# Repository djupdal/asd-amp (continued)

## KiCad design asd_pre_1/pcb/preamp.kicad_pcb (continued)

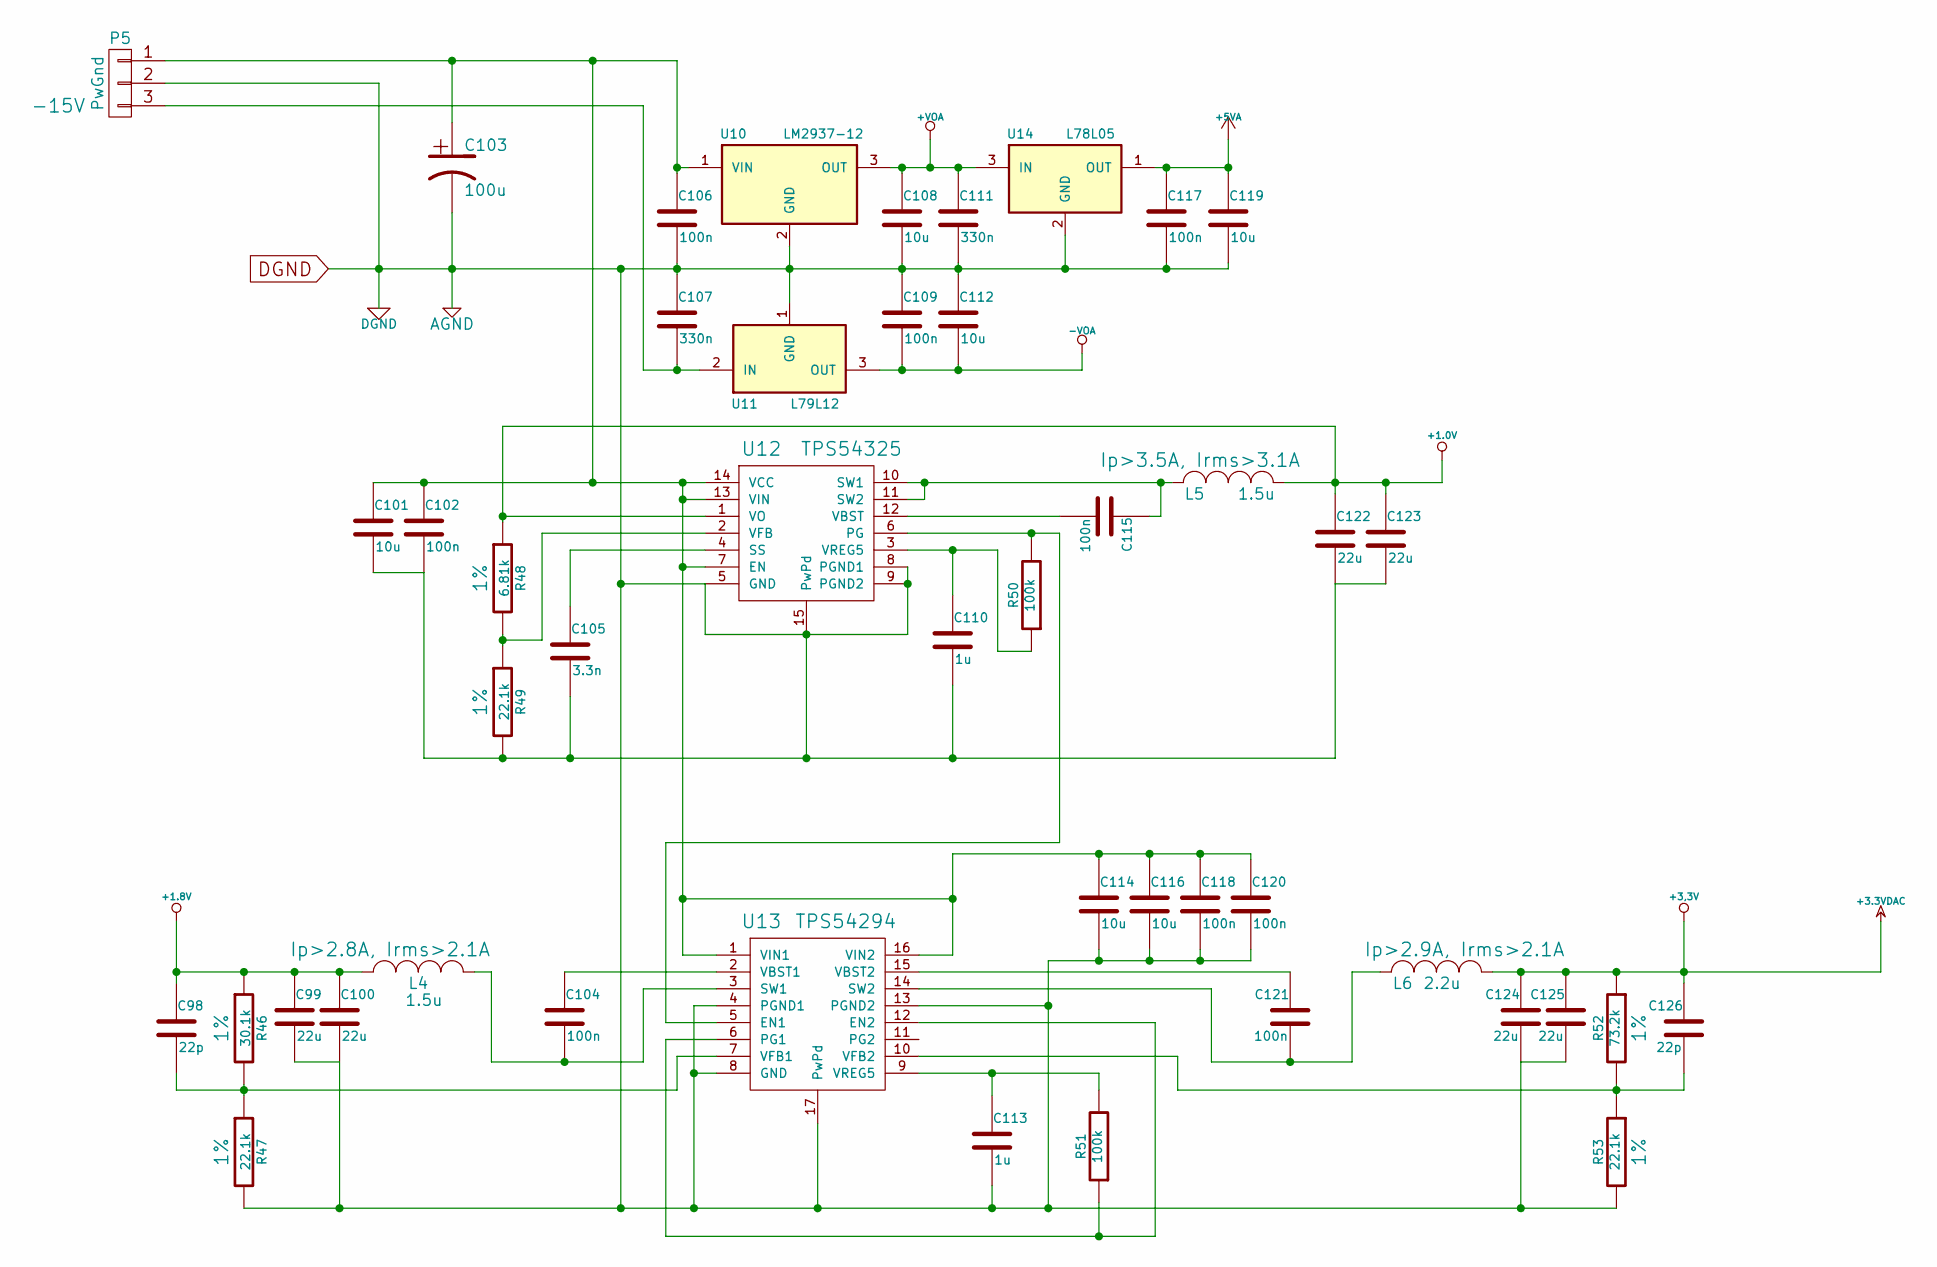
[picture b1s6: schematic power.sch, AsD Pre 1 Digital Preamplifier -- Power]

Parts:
C98, C126: 22p; C_0603_HandSoldering
C99, C100, C122, C123, C124, C125: 22u; C_0805_HandSoldering
C101, C108, C112, C114, C116, C119: 10u; C_0805_HandSoldering
C102, C104, C106, C109, C115, C117, C118, C120, C121: 100n; C_0603_HandSoldering
C103: 100u; TantalC_SizeB_EIA-3528_HandSoldering
C105: 3.3n; C_0603_HandSoldering
C107, C111: 330n; C_0603_HandSoldering
C110, C113: 1u; C_0805_HandSoldering
L4, L5: 1.5u; SPM3015
L6: 2.2u; SPM3015
P5: PwGnd; Terminal_Block_3_5mm
R46: 30.1k; R_0805_HandSoldering
R47, R49, R53: 22.1k; R_0805_HandSoldering
R48: 6.81k; R_0805_HandSoldering
R50, R51: 100k; R_0805_HandSoldering
R52: 73.2k; R_0805_HandSoldering
U10: LM2937-12; SOT-223
U11: L79L12; SOT89-3_Housing_Handsoldering
U12: TPS54325; TSSOP-14_4.4x5mm_Pitch0.65mm_exposed_pad
U13: TPS54294; TSSOP-16-1EP_4.4x5mm_Pitch0.65mm
U14: L78L05; SOT89-3_Housing_Handsoldering

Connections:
+1.0V: C122.1, C123.1, L5.2, R48.1, U12.1 (VO); also elsewhere on the board
+1.8V: C98.1, C99.1, C100.1, L4.1, R46.1; also elsewhere on the board
+3.3V: C124.1, C125.1, C126.1, L6.1, R52.1; also elsewhere on the board
+5VA: C117.1, C119.1, U14.1 (OUT); also elsewhere on the board
+VOA: C108.1, C111.1, U10.3 (OUT), U14.3 (IN); also elsewhere on the board
-VOA: C109.2, C112.2, U11.3 (OUT); also elsewhere on the board
DGND: C99.2, C100.2, C101.2, C102.2, C103.2, C105.2, C106.2, C107.1, C108.2, C109.1, C110.2, C111.2, C112.1, C113.2, C114.2, C116.2, C117.2, C118.2, C119.2, C120.2, C122.2, C123.2, C124.2, C125.2, P5.2, R47.2, R49.2, R53.2, U10.2 (GND), U11.1 (GND), U12.5 (GND), U12.8 (PGND1), U12.9 (PGND2), U12.15 (PwPd), U13.4 (PGND1), U13.8 (GND), U13.13 (PGND2), U13.17 (PwPd), U14.2 (GND); also elsewhere on the board
unnamed: C98.2, R46.2, R47.1, U13.7 (VFB1)
unnamed: C101.1, C102.1, C103.1, C106.1, C114.1, C116.1, C118.1, C120.1, P5.1, U10.1 (VIN), U12.7 (EN), U12.13 (VIN), U12.14 (VCC), U13.1 (VIN1), U13.16 (VIN2)
unnamed: C104.1, U13.2 (VBST1)
unnamed: C104.2, L4.2, U13.3 (SW1)
unnamed: C105.1, U12.4 (SS)
unnamed: C107.2, P5.3, U11.2 (IN)
unnamed: C110.1, R50.1, U12.3 (VREG5)
unnamed: C113.1, R51.2, U13.9 (VREG5)
unnamed: C115.1, L5.1, U12.10 (SW1), U12.11 (SW2)
unnamed: C115.2, U12.12 (VBST)
unnamed: C121.1, U13.15 (VBST2)
unnamed: C121.2, L6.2, U13.14 (SW2)
unnamed: C126.2, R52.2, R53.1, U13.10 (VFB2)
unnamed: R48.2, R49.1, U12.2 (VFB)
unnamed: R50.2, U12.6 (PG), U13.5 (EN1)
unnamed: R51.1, U13.6 (PG1), U13.12 (EN2)

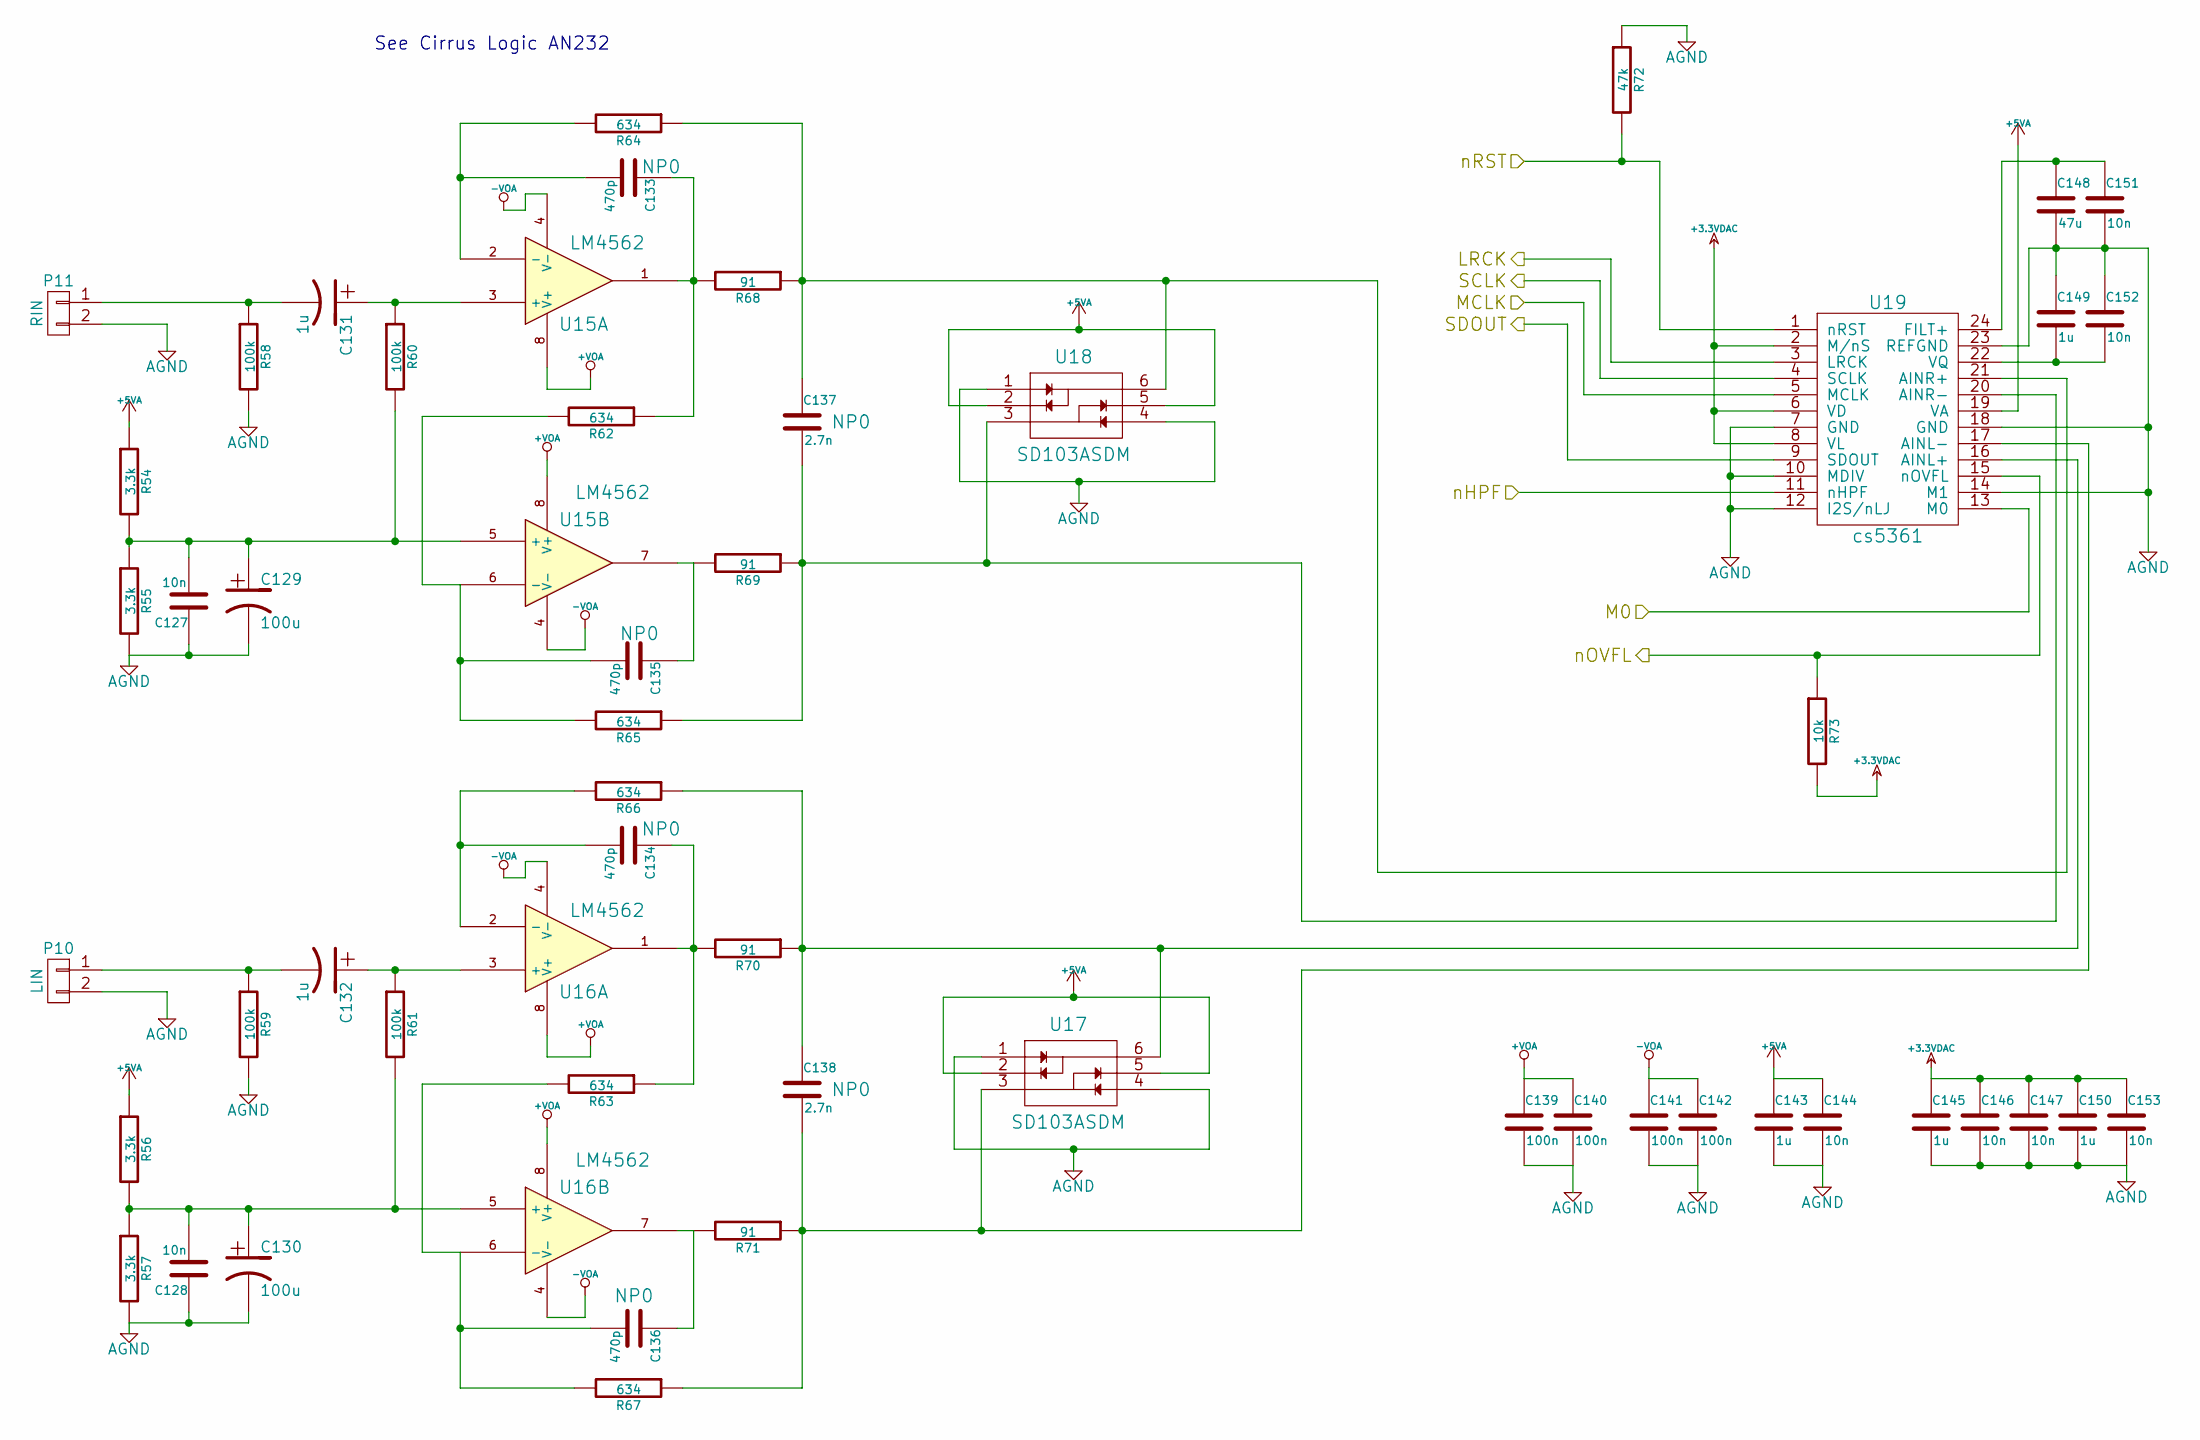
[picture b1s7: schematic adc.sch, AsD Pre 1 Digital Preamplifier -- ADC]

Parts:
C127, C128, C144, C146, C147, C151, C152, C153: 10n; C_0603_HandSoldering
C129, C130: 100u; TantalC_SizeB_EIA-3528_HandSoldering
C131, C132, C143, C145, C149, C150: 1u; C_0805_HandSoldering
C133, C134, C135, C136: 470p; C_0603_HandSoldering
C137, C138: 2.7n; C_0603_HandSoldering
C139, C140, C141, C142: 100n; C_0603_HandSoldering
C148: 47u; C_1210_HandSoldering
P10: LIN; Terminal_Block_2_2.5mm
P11: RIN; Terminal_Block_2_2.5mm
R54, R55, R56, R57: 3.3k; R_0805_HandSoldering
R58, R59, R60, R61: 100k; R_0805_HandSoldering
R62, R63, R64, R65, R66, R67: 634; R_0805_HandSoldering
R68, R69, R70, R71: 91; R_0805_HandSoldering
R72: 47k; R_0805_HandSoldering
R73: 10k; R_0805_HandSoldering
U15, U16: LM4562; SOIC-8-W
U17, U18: SD103ASDM; SOT-26-6
U19: cs5361; TSSOP-24_4.4x7.8mm_Pitch0.65mm

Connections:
+3.3V: C145.1, C146.1, C147.1, C150.1, C153.1, R73.2, U19.2 (M/nS), U19.6 (VD), U19.8 (VL); also elsewhere on the board
+5VA: C143.1, C144.1, R54.1, R56.1, U17.2, U17.5, U18.2, U18.5, U19.19 (VA); also elsewhere on the board
+VOA: C139.1, C140.1, U15.8 (V+), U16.8 (V+); also elsewhere on the board
-VOA: C141.1, C142.1, U15.4 (V-), U16.4 (V-); also elsewhere on the board
/ADC/LRCK: U19.3 (LRCK); also elsewhere on the board
/ADC/M0: U19.13 (M0); also elsewhere on the board
/ADC/MCLK: U19.5 (MCLK); also elsewhere on the board
/ADC/nHPF: U19.11 (nHPF); also elsewhere on the board
/ADC/nOVFL: R73.1, U19.15 (nOVFL); also elsewhere on the board
/ADC/nRST: R72.2, U19.1 (nRST); also elsewhere on the board
/FPGA/BCKI2: U19.4 (SCLK); also elsewhere on the board
/FPGA/DIN2: U19.9 (SDOUT); also elsewhere on the board
DGND: C127.1, C128.1, C129.2, C130.2, C139.2, C140.2, C141.2, C142.2, C143.2, C144.2, C145.2, C146.2, C147.2, C148.2, C149.1, C150.2, C151.2, C152.1, C153.2, P10.2, P11.2, R55.2, R57.2, R58.2, R59.2, R72.1, U17.1, U17.4, U18.1, U18.4, U19.7 (GND), U19.10 (MDIV), U19.12 (I2S/nLJ), U19.14 (M1), U19.18 (GND), U19.23 (REFGND); also elsewhere on the board
unnamed: C127.2, C129.1, R54.2, R55.1, R60.2, U15.5 (+)
unnamed: C128.2, C130.1, R56.2, R57.1, R61.2, U16.5 (+)
unnamed: C131.1, R60.1, U15.3 (+)
unnamed: C131.2, P11.1, R58.1
unnamed: C132.1, R61.1, U16.3 (+)
unnamed: C132.2, P10.1, R59.1
unnamed: C133.1, R62.1, R68.2, U15.1
unnamed: C133.2, R64.2, U15.2 (-)
unnamed: C134.1, R63.1, R70.2, U16.1
unnamed: C134.2, R66.2, U16.2 (-)
unnamed: C135.1, R69.2, U15.7
unnamed: C135.2, R62.2, R65.2, U15.6 (-)
unnamed: C136.1, R71.2, U16.7
unnamed: C136.2, R63.2, R67.2, U16.6 (-)
unnamed: C137.1, R64.1, R68.1, U18.6, U19.21 (AINR+)
unnamed: C137.2, R65.1, R69.1, U18.3, U19.20 (AINR-)
unnamed: C138.1, R66.1, R70.1, U17.6, U19.16 (AINL+)
unnamed: C138.2, R67.1, R71.1, U17.3, U19.17 (AINL-)
unnamed: C148.1, C151.1, U19.24 (FILT+)
unnamed: C149.2, C152.2, U19.22 (VQ)

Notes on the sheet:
See Cirrus Logic AN232

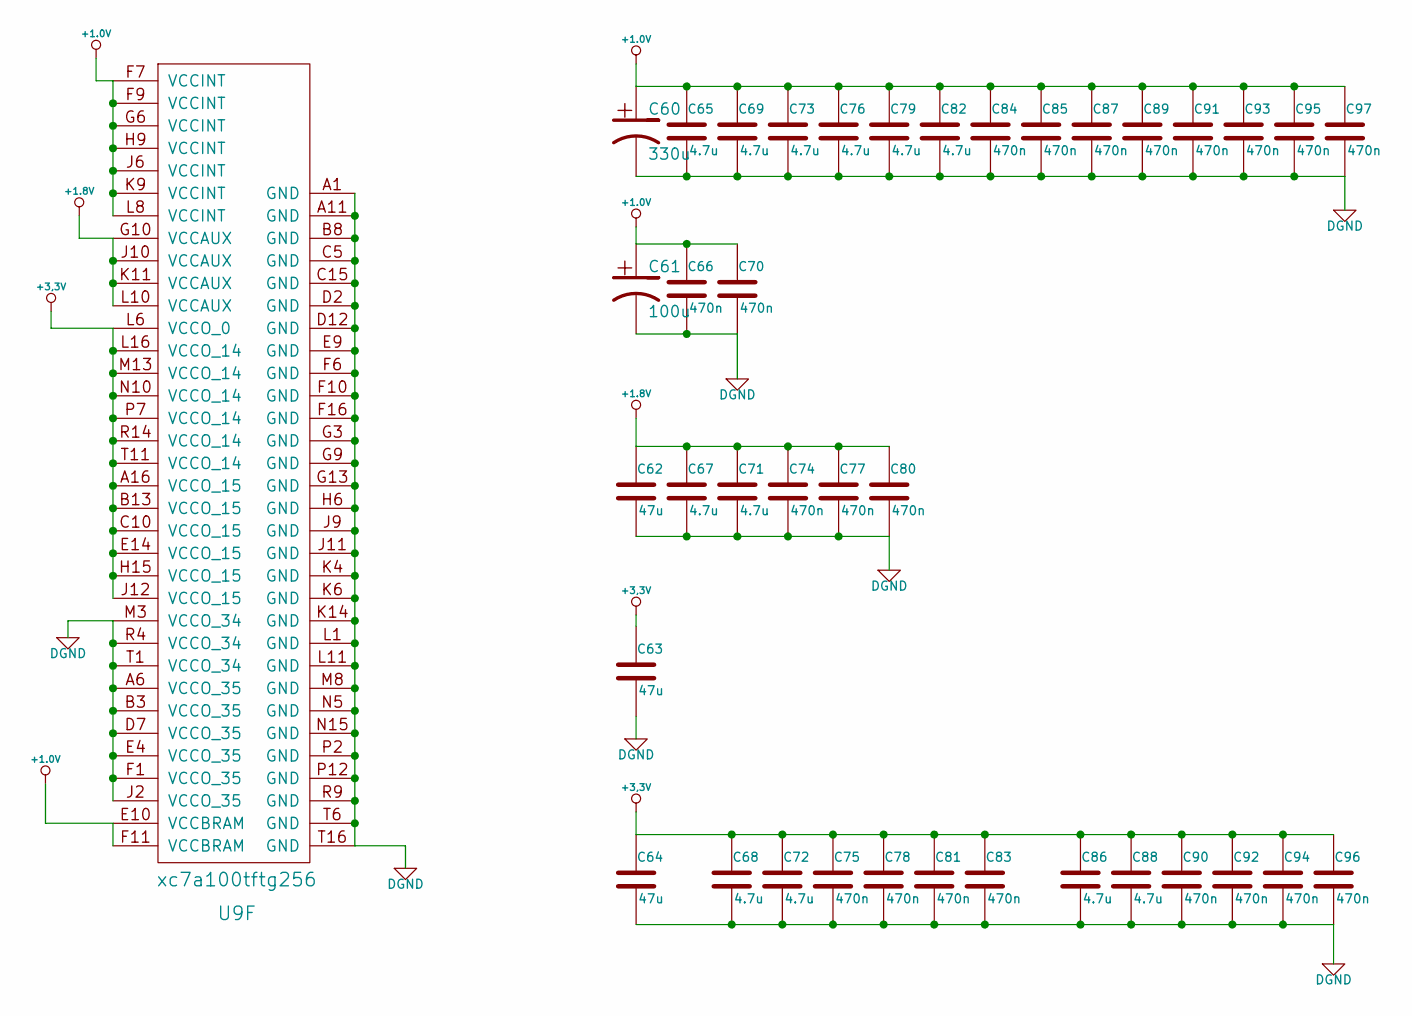
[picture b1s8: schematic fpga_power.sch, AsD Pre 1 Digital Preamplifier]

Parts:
C60: 330u; TantalC_SizeD_EIA-7343_HandSoldering
C61: 100u; TantalC_SizeB_EIA-3528_HandSoldering
C62, C63, C64: 47u; C_1210_HandSoldering
C65, C67, C68, C69, C71, C72, C73, C76, C79, C82, C86, C88: 4.7u; C_0805_HandSoldering
C66, C70, C74, C75, C77, C78, C80, C81, C83, C84, C85, C87, C89, C90, C91, C92, C93, C94, C95, C96, C97: 470n; C_0603_HandSoldering
U9: xc7a100tftg256; FTG256

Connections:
+1.0V: C60.1, C61.1, C65.1, C66.1, C69.1, C70.1, C73.1, C76.1, C79.1, C82.1, C84.1, C85.1, C87.1, C89.1, C91.1, C93.1, C95.1, C97.1, U9.E10 (VCCBRAM), U9.F7 (VCCINT), U9.F9 (VCCINT), U9.F11 (VCCBRAM), U9.G6 (VCCINT), U9.H9 (VCCINT), U9.J6 (VCCINT), U9.K9 (VCCINT), U9.L8 (VCCINT); also elsewhere on the board
+1.8V: C62.1, C67.1, C71.1, C74.1, C77.1, C80.1, U9.G10 (VCCAUX), U9.J10 (VCCAUX), U9.K11 (VCCAUX), U9.L10 (VCCAUX); also elsewhere on the board
+3.3V: C63.1, C64.1, C68.1, C72.1, C75.1, C78.1, C81.1, C83.1, C86.1, C88.1, C90.1, C92.1, C94.1, C96.1, U9.A16 (VCCO_15), U9.B13 (VCCO_15), U9.C10 (VCCO_15), U9.E14 (VCCO_15), U9.H15 (VCCO_15), U9.J12 (VCCO_15), U9.L6 (VCCO_0), U9.L16 (VCCO_14), U9.M13 (VCCO_14), U9.N10 (VCCO_14), U9.P7 (VCCO_14), U9.R14 (VCCO_14), U9.T11 (VCCO_14); also elsewhere on the board
DGND: C60.2, C61.2, C62.2, C63.2, C64.2, C65.2, C66.2, C67.2, C68.2, C69.2, C70.2, C71.2, C72.2, C73.2, C74.2, C75.2, C76.2, C77.2, C78.2, C79.2, C80.2, C81.2, C82.2, C83.2, C84.2, C85.2, C86.2, C87.2, C88.2, C89.2, C90.2, C91.2, C92.2, C93.2, C94.2, C95.2, C96.2, C97.2, U9.A1 (GND), U9.A6 (VCCO_35), U9.A11 (GND), U9.B3 (VCCO_35), U9.B8 (GND), U9.C5 (GND), U9.C15 (GND), U9.D2 (GND), U9.D7 (VCCO_35), U9.D12 (GND), U9.E4 (VCCO_35), U9.E9 (GND), U9.F1 (VCCO_35), U9.F6 (GND), U9.F10 (GND), U9.F16 (GND), U9.G3 (GND), U9.G9 (GND), U9.G13 (GND), U9.H6 (GND), U9.J2 (VCCO_35), U9.J9 (GND), U9.J11 (GND), U9.K4 (GND), U9.K6 (GND), U9.K14 (GND), U9.L1 (GND), U9.L11 (GND), U9.M3 (VCCO_34), U9.M8 (GND), U9.N5 (GND), U9.N15 (GND), U9.P2 (GND), U9.P12 (GND), U9.R4 (VCCO_34), U9.R9 (GND), U9.T1 (VCCO_34), U9.T6 (GND), U9.T16 (GND); also elsewhere on the board

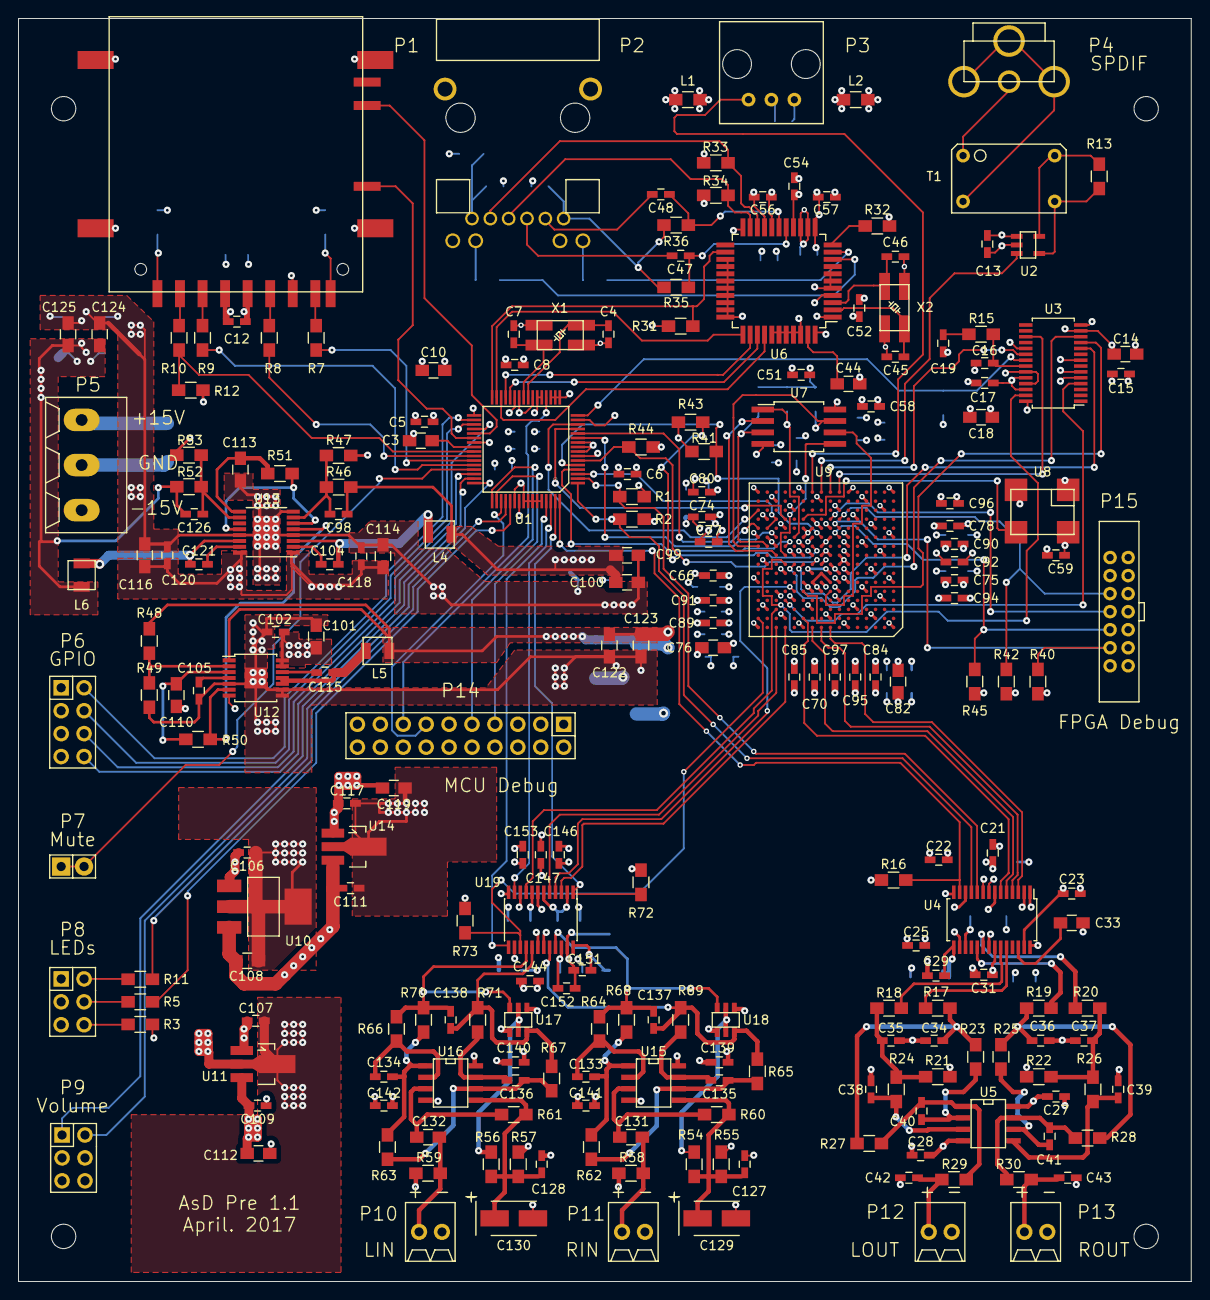
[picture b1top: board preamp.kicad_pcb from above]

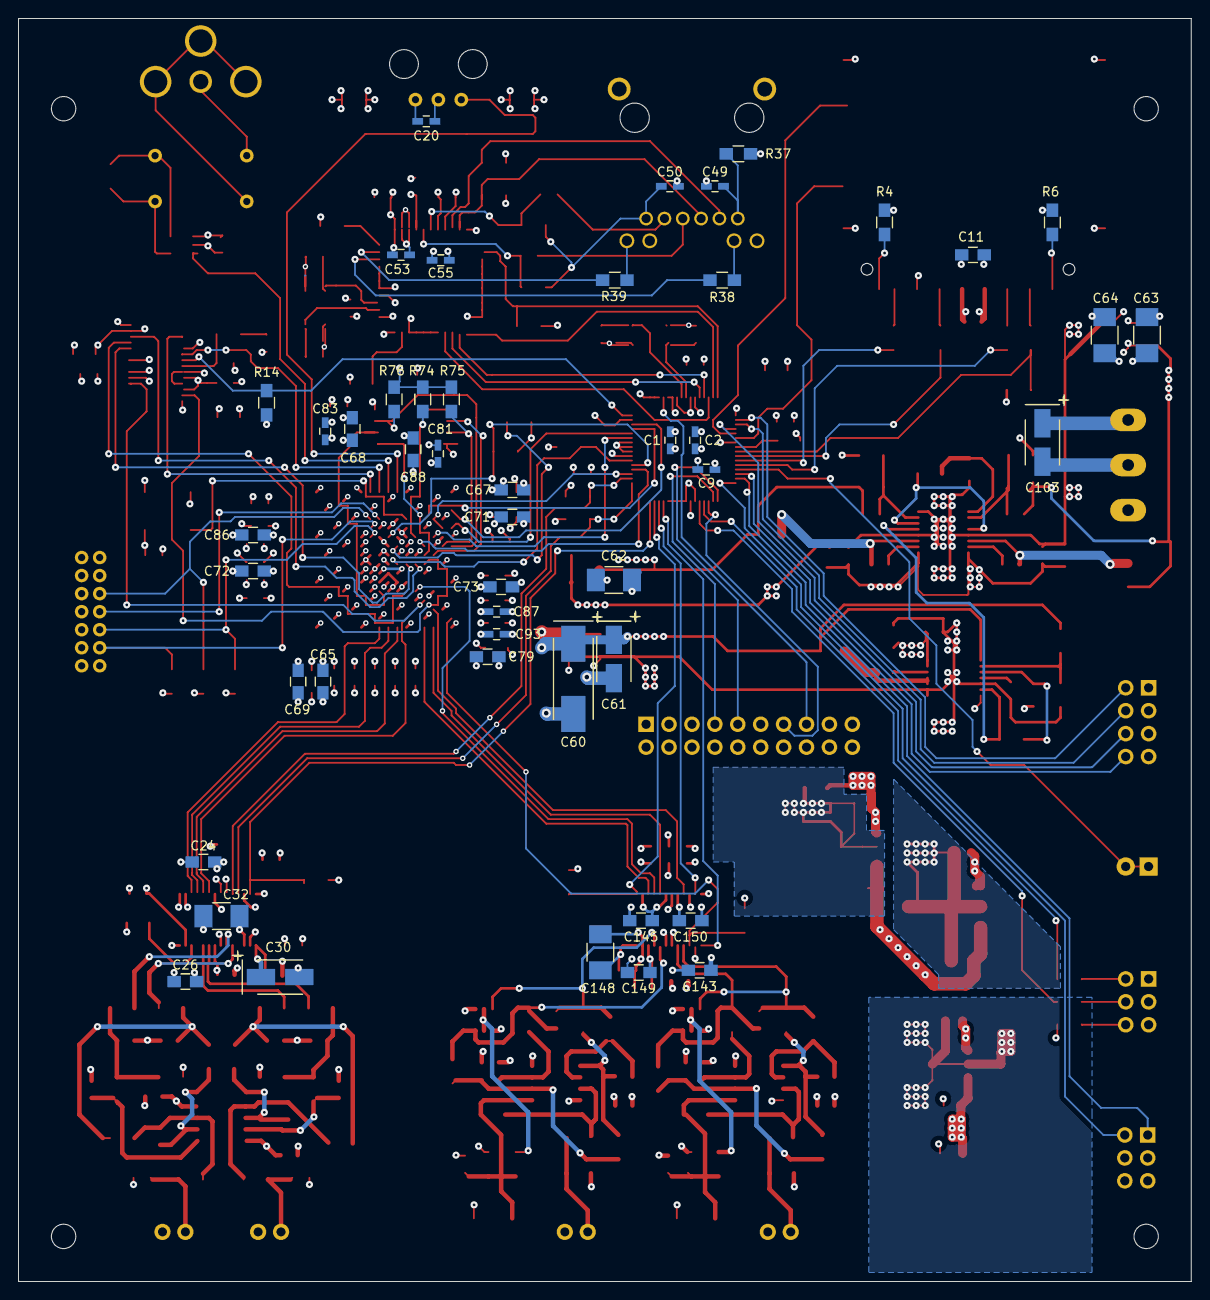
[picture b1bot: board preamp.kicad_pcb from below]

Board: 4 copper layers, 130.0 x 140.0 mm, 275 parts (47 on the bottom side), 166 nets.

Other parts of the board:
MountingHole_2-7mm, MountingHole_2-7mm#2, MountingHole_2-7mm#3, MountingHole_2-7mm#4: VAL**; MountingHole_2-7mm

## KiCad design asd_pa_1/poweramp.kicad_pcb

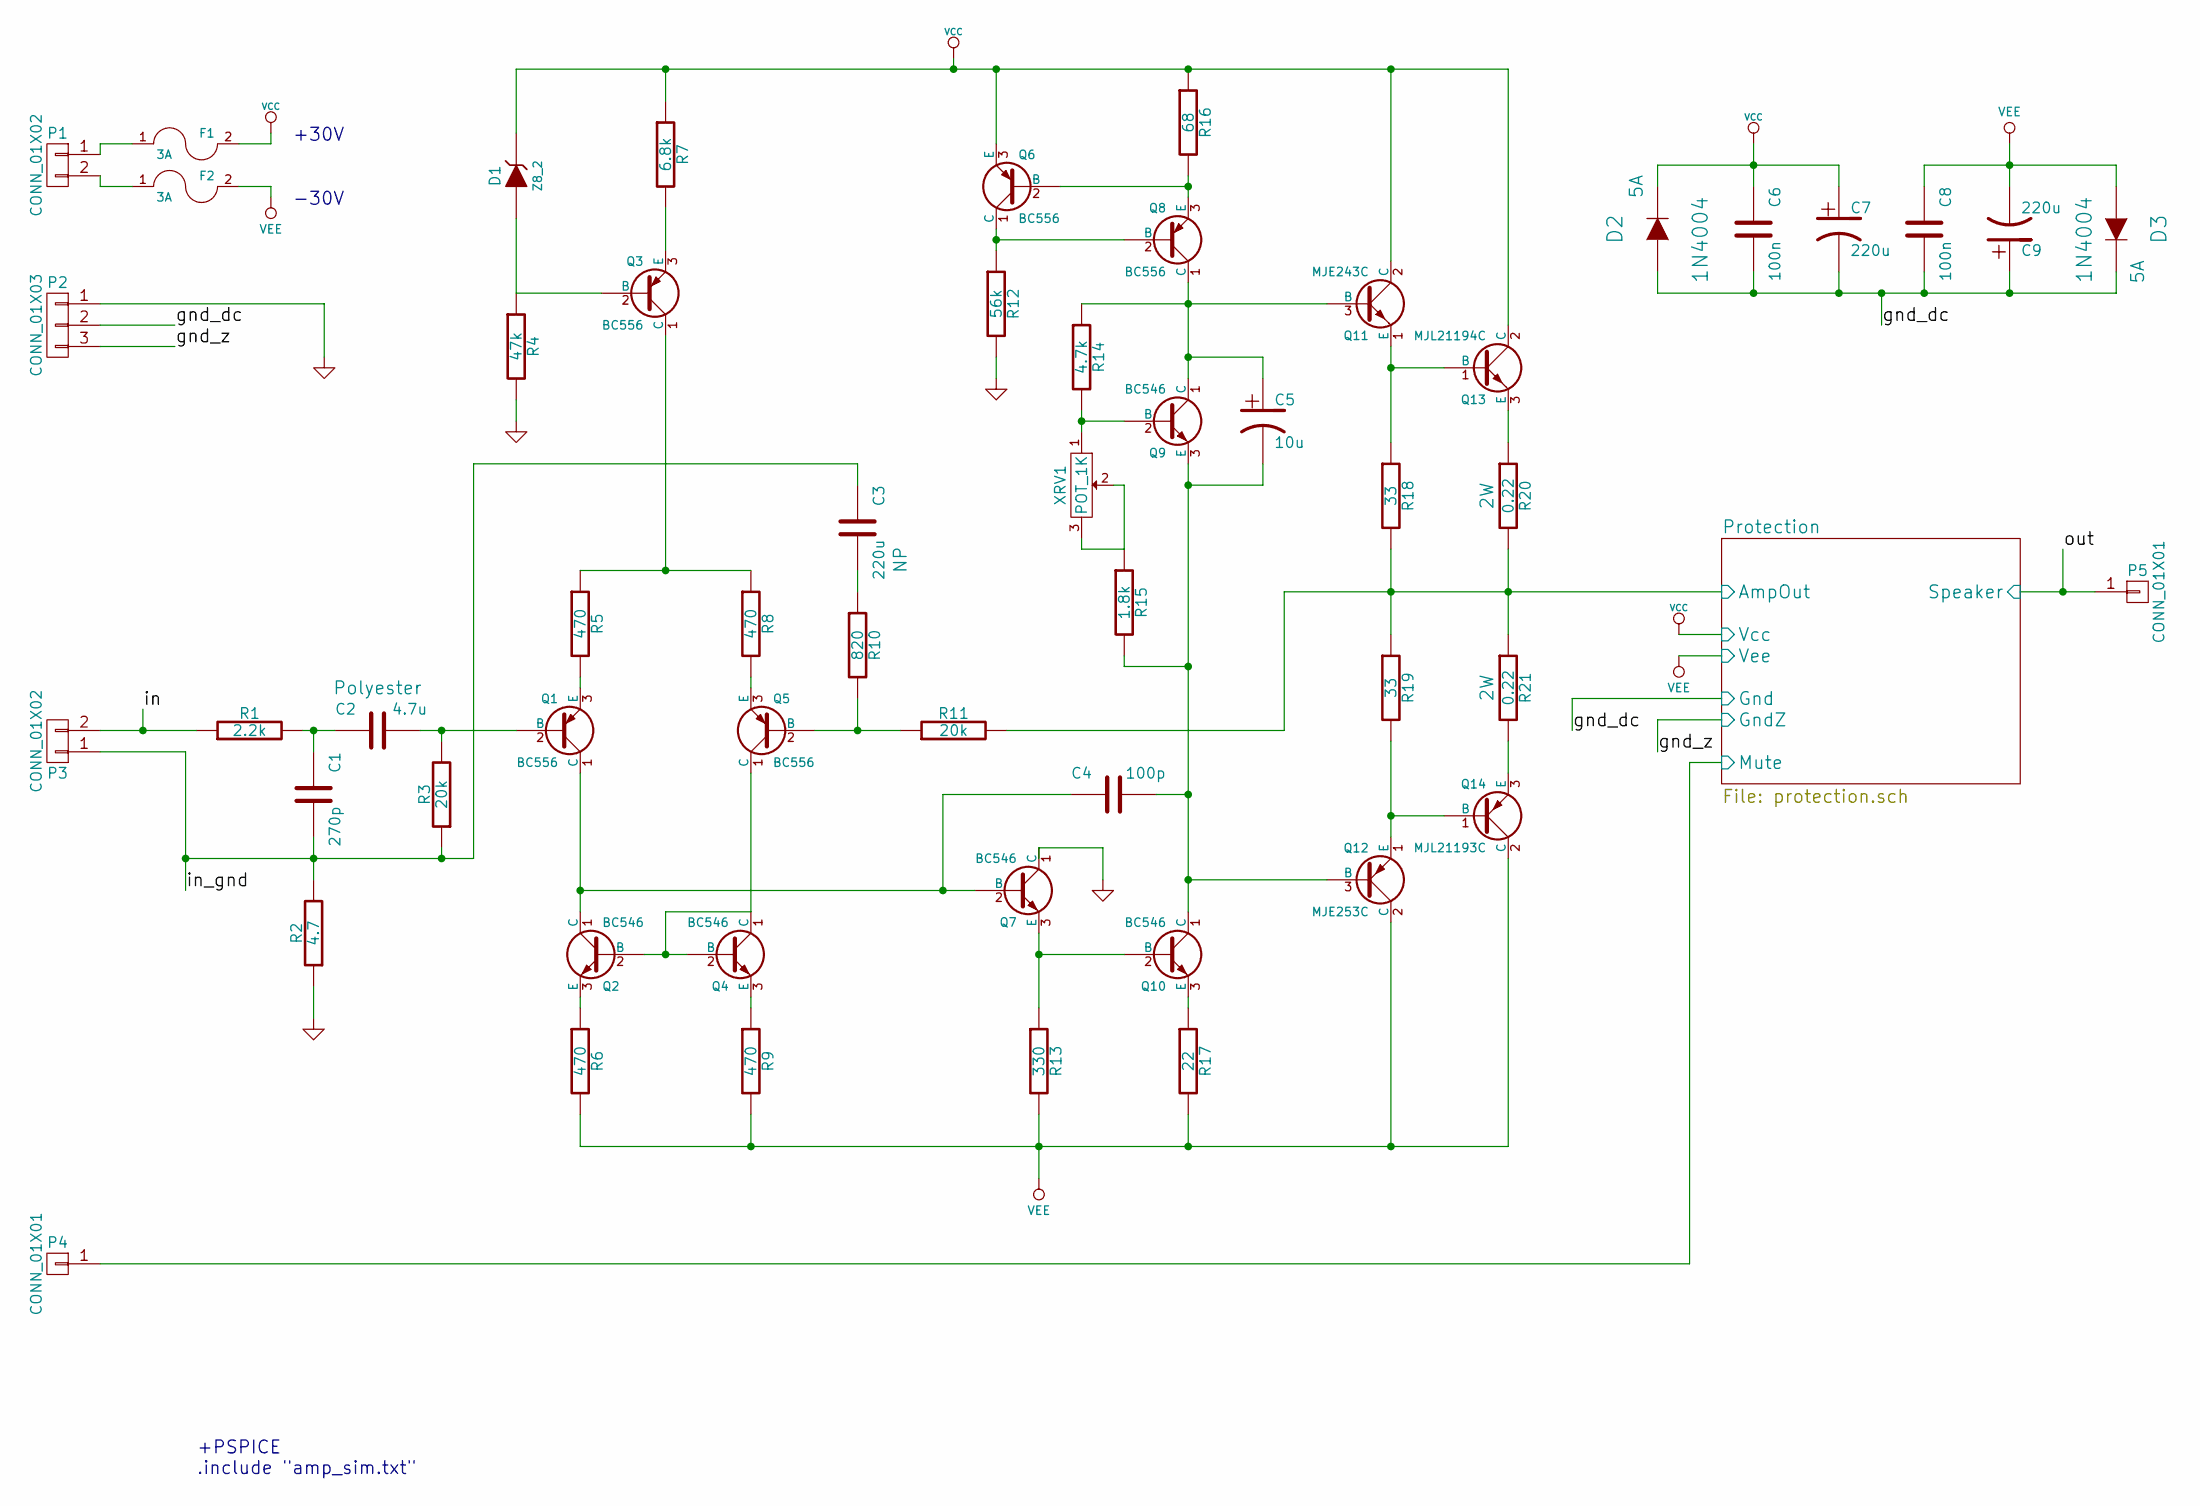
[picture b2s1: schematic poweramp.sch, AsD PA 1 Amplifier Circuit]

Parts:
C1: 270p; Capacitor7x2.5RM5
C2: 4.7u; Kemet_4.7u_Polyester
C3: 220u; 220u_NP
C4: 100p; Capacitor7x2.5RM5
C5: 10u; Capacitor5x11RM2.5
C6, C8: 100n; Capacitor7x2.5RM5
C7, C9: 220u; Capacitor10x25RM2.5
D1: Z8_2; Diode_DO-41_SOD81_Horizontal_RM10
D2, D3: 1N4004; Diode_DO-41_SOD81_Horizontal_RM10
F1, F2: 3A; Resistor_Horizontal_RM10mm
P1: CONN_01X02; Terminal_Block_2_5mm
P2: CONN_01X03; Terminal_Block_3_5mm
P3: CONN_01X02; Terminal_Block_2_2.5mm
P4: CONN_01X01; Pin_Header_Straight_1x01
P5: CONN_01X01; Screw_Terminal
Q1, Q3, Q5, Q6, Q8: BC556; TO-92-Free-inline-narrow-oval
Q2, Q4, Q7, Q9, Q10: BC546; TO-92-Free-inline-narrow-oval
Q11: MJE243C; TO-220_Neutral123_Vertical
Q12: MJE253C; TO-220_Neutral123_Vertical
Q13: MJL21194C; TO-247_Vertical_Neutral123
Q14: MJL21193C; TO-247_Vertical_Neutral123
R1: 2.2k; Resistor_Horizontal_RM10mm
R2: 4.7; Resistor_Horizontal_RM10mm
R3, R11: 20k; Resistor_Horizontal_RM10mm
R4: 47k; Resistor_Horizontal_RM10mm
R5, R6, R8, R9: 470; Resistor_Horizontal_RM10mm
R7: 6.8k; Resistor_Horizontal_RM10mm
R10: 820; Resistor_Horizontal_RM10mm
R12: 56k; Resistor_Horizontal_RM10mm
R13: 330; Resistor_Horizontal_RM10mm
R14: 4.7k; Resistor_Horizontal_RM10mm
R15: 1.8k; Resistor_Horizontal_RM10mm
R16: 68; Resistor_Horizontal_RM10mm
R17: 22; Resistor_Horizontal_RM10mm
R18, R19: 33; Resistor_Horizontal_RM10mm
R20, R21: 0.22; Resistor_Horizontal_RM20mm
XRV1: POT_1K; Potentiometer_Bourns_3296W_3-8Zoll_Inline_ScrewUp

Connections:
/Protection/AmpOut: R11.2, R18.2, R19.1, R20.2, R21.1; also elsewhere on the board
/Protection/Gnd: C6.2, C7.2, C8.2, C9.1, D2.1 (A), D3.2 (K), P2.2; also elsewhere on the board
/Protection/GndZ: P2.3; also elsewhere on the board
/Protection/Mute: P4.1; also elsewhere on the board
/Protection/Speaker: P5.1; also elsewhere on the board
/in: P3.2, R1.1
/in_gnd: C1.2, C3.1, P3.1, R2.2, R3.1
GND: P2.1, Q7.1 (C), R2.1, R4.2, R12.2
unnamed: C1.1, C2.1, R1.2
unnamed: C2.2, Q1.2 (B), R3.2
unnamed: C3.2, R10.1
unnamed: C4.1, Q1.1 (C), Q2.1 (C), Q7.2 (B)
unnamed: C4.2, C5.2, Q9.3 (E), Q10.1 (C), Q12.3 (B), R15.2
unnamed: C5.1, Q8.1 (C), Q9.1 (C), Q11.3 (B), R14.1
unnamed: D1.1 (A), Q3.2 (B), R4.1
unnamed: F1.1, P1.1
unnamed: F2.1, P1.2
unnamed: Q1.3 (E), R5.2
unnamed: Q2.2 (B), Q4.1 (C), Q4.2 (B), Q5.1 (C)
unnamed: Q2.3 (E), R6.1
unnamed: Q3.1 (C), R5.1, R8.1
unnamed: Q3.3 (E), R7.2
unnamed: Q4.3 (E), R9.1
unnamed: Q5.2 (B), R10.2, R11.1
unnamed: Q5.3 (E), R8.2
unnamed: Q6.1 (C), Q8.2 (B), R12.1
unnamed: Q6.2 (B), Q8.3 (E), R16.2
unnamed: Q9.2 (B), R14.2, XRV1.1
unnamed: Q7.3 (E), Q10.2 (B), R13.1
unnamed: Q10.3 (E), R17.1
unnamed: Q11.1 (E), Q13.1 (B), R18.1
unnamed: Q12.1 (E), Q14.1 (B), R19.2
unnamed: Q13.3 (E), R20.1
unnamed: Q14.3 (E), R21.2
unnamed: R15.1, XRV1.2, XRV1.3
VCC: C6.1, C7.1, D1.2 (K), D2.2 (K), F1.2, Q6.3 (E), Q11.2 (C), Q13.2 (C), R7.1, R16.1; also elsewhere on the board
VEE: C8.1, C9.2, D3.1 (A), F2.2, Q12.2 (C), Q14.2 (C), R6.2, R9.2, R13.2, R17.2; also elsewhere on the board

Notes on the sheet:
-30V
+30V
+PSPICE .include "amp_sim.txt"
